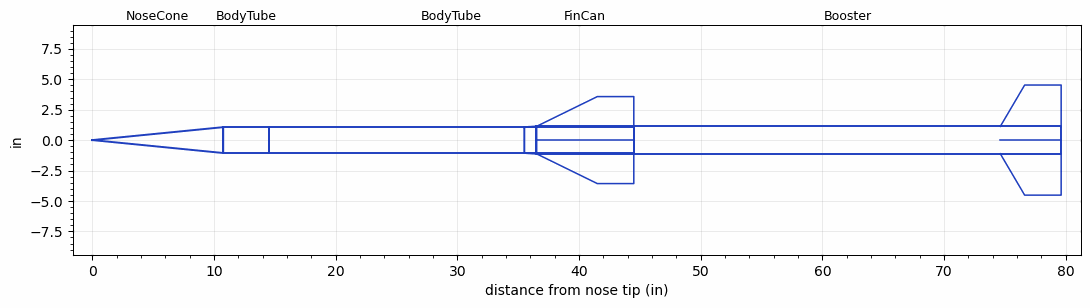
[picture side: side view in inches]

<RASAeroDocument>
 <FileVersion>2</FileVersion>
 <RocketDesign>
  <NoseCone>
   <Length>10.75</Length>
   <Diameter>2.125</Diameter>
   <Shape>Conical</Shape>
   <BluntRadius>0.0625</BluntRadius>
   <Location>0</Location>
  </NoseCone>
  <BodyTube>
   <Length>3.75</Length>
   <Diameter>2.125</Diameter>
   <Location>10.75</Location>
  </BodyTube>
  <BodyTube>
   <Length>30</Length>
   <Diameter>2.125</Diameter>
   <Location>14.5</Location>
  </BodyTube>
  <FinCan>
   <Length>8</Length>
   <Diameter>2.25</Diameter>
   <InsideDiameter>2.125</InsideDiameter>
   <Location>44.5</Location>
   <ShoulderLength>1</ShoulderLength>
   <Offset>-8</Offset>
   <Fin>
    <Count>4</Count>
    <Chord>8</Chord>
    <Span>2.45</Span>
    <SweepDistance>5</SweepDistance>
    <TipChord>3</TipChord>
    <Thickness>0.125</Thickness>
    <LERadius>0.02</LERadius>
    <Location>8</Location>
    <AirfoilSection>Double Wedge</AirfoilSection>
    <FX1>1.5</FX1>
    <FX3>0.5</FX3>
   </Fin>
  </FinCan>
  <Booster>
   <Length>35.125</Length>
   <Diameter>2.25</Diameter>
   <InsideDiameter>2.25</InsideDiameter>
   <Location>44.5</Location>
   <ShoulderLength>0</ShoulderLength>
   <Fin>
    <Count>4</Count>
    <Chord>5</Chord>
    <Span>3.4</Span>
    <SweepDistance>2</SweepDistance>
    <TipChord>3</TipChord>
    <Thickness>0.455</Thickness>
    <LERadius>0.02</LERadius>
    <Location>5</Location>
    <AirfoilSection>Double Wedge</AirfoilSection>
    <FX1>1.5</FX1>
    <FX3>1.5</FX3>
   </Fin>
  </Booster>
  <Surface>Camouflage Paint</Surface>
  <ModifiedBarrowman>True</ModifiedBarrowman>
  <Turbulence>True</Turbulence>
  <UseBooster1>False</UseBooster1>
  <UseBooster2>False</UseBooster2>
 </RocketDesign>
 <LaunchSite>
  <Altitude>2000</Altitude>
  <Pressure>0</Pressure>
  <RodAngle>2</RodAngle>
  <RodLength>10</RodLength>
  <Temperature>50</Temperature>
  <WindSpeed>7</WindSpeed>
 </LaunchSite>
 <Recovery>
  <Altitude1>1000</Altitude1>
  <Altitude2>3000</Altitude2>
  <DeviceType1>Parachute</DeviceType1>
  <DeviceType2>Parachute</DeviceType2>
  <Event1>False</Event1>
  <Event2>False</Event2>
  <Size1>6</Size1>
  <Size2>24</Size2>
  <EventType1>Apogee</EventType1>
  <EventType2>Altitude</EventType2>
  <CD1>0.75</CD1>
  <CD2>1.8</CD2>
 </Recovery>
 <SimulationList>
  <Simulation>
   <SustainerEngine>L1081  (boostkareilley)</SustainerEngine>
   <SustainerLaunchWt>8</SustainerLaunchWt>
   <SustainerNozzleDiameter>1.9</SustainerNozzleDiameter>
   <SustainerCG>29.5</SustainerCG>
   <SustainerIgnitionDelay>0.2</SustainerIgnitionDelay>
   <Booster1Engine>L1553ChBNC  (Polaris)</Booster1Engine>
   <Booster1LaunchWt>15.6</Booster1LaunchWt>
   <Booster1SeparationDelay>0</Booster1SeparationDelay>
   <Booster1IgnitionDelay>0</Booster1IgnitionDelay>
   <Booster1CG>47</Booster1CG>
   <Booster1NozzleDiameter>1.9</Booster1NozzleDiameter>
   <IncludeBooster1>True</IncludeBooster1>
   <Booster2Delay>0</Booster2Delay>
   <IncludeBooster2>False</IncludeBooster2>
   <TimetoApogee>45.82866</TimetoApogee>
   <MaxAltitude>50880.7</MaxAltitude>
   <MaxVelocity>4342.401</MaxVelocity>
  </Simulation>
 </SimulationList>
</RASAeroDocument>
